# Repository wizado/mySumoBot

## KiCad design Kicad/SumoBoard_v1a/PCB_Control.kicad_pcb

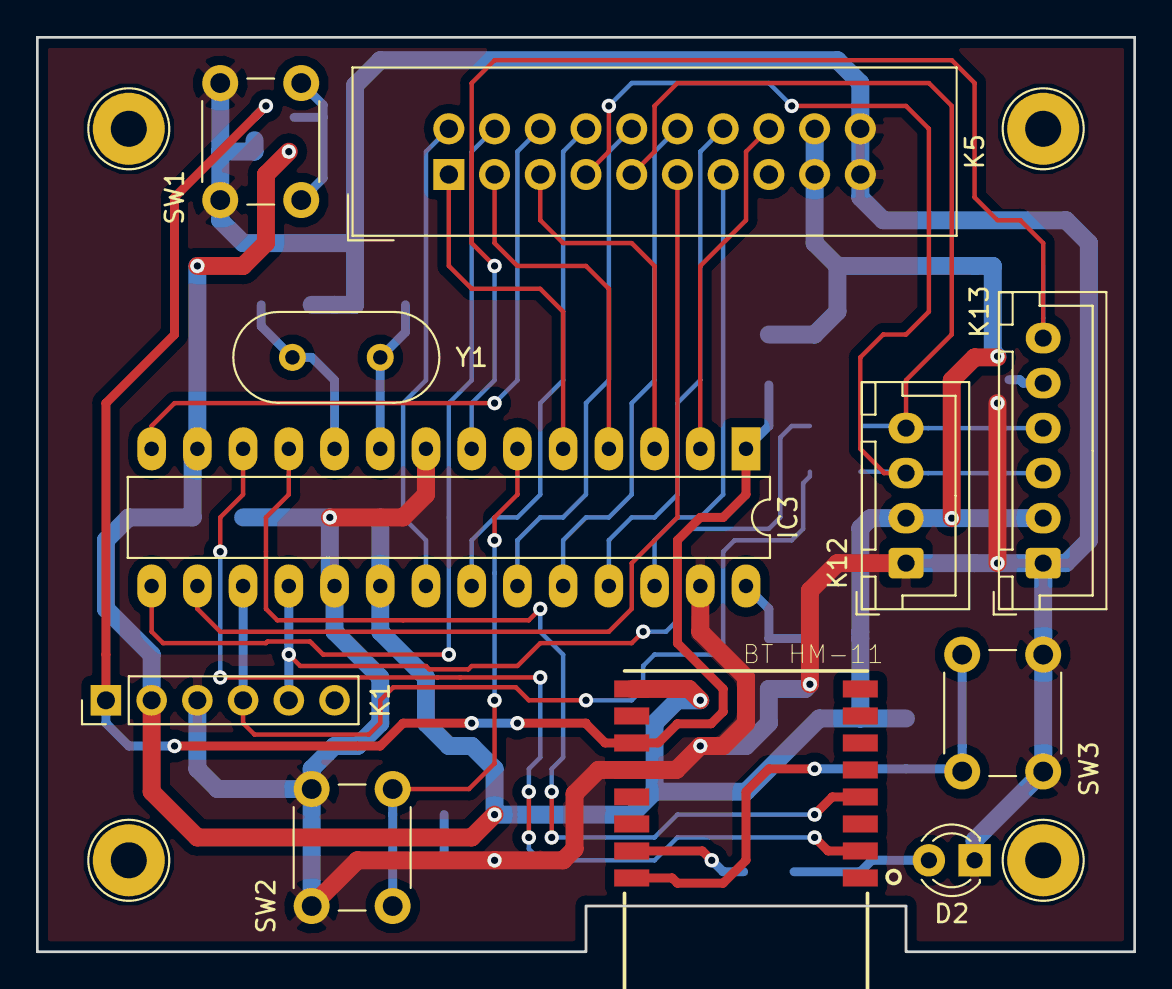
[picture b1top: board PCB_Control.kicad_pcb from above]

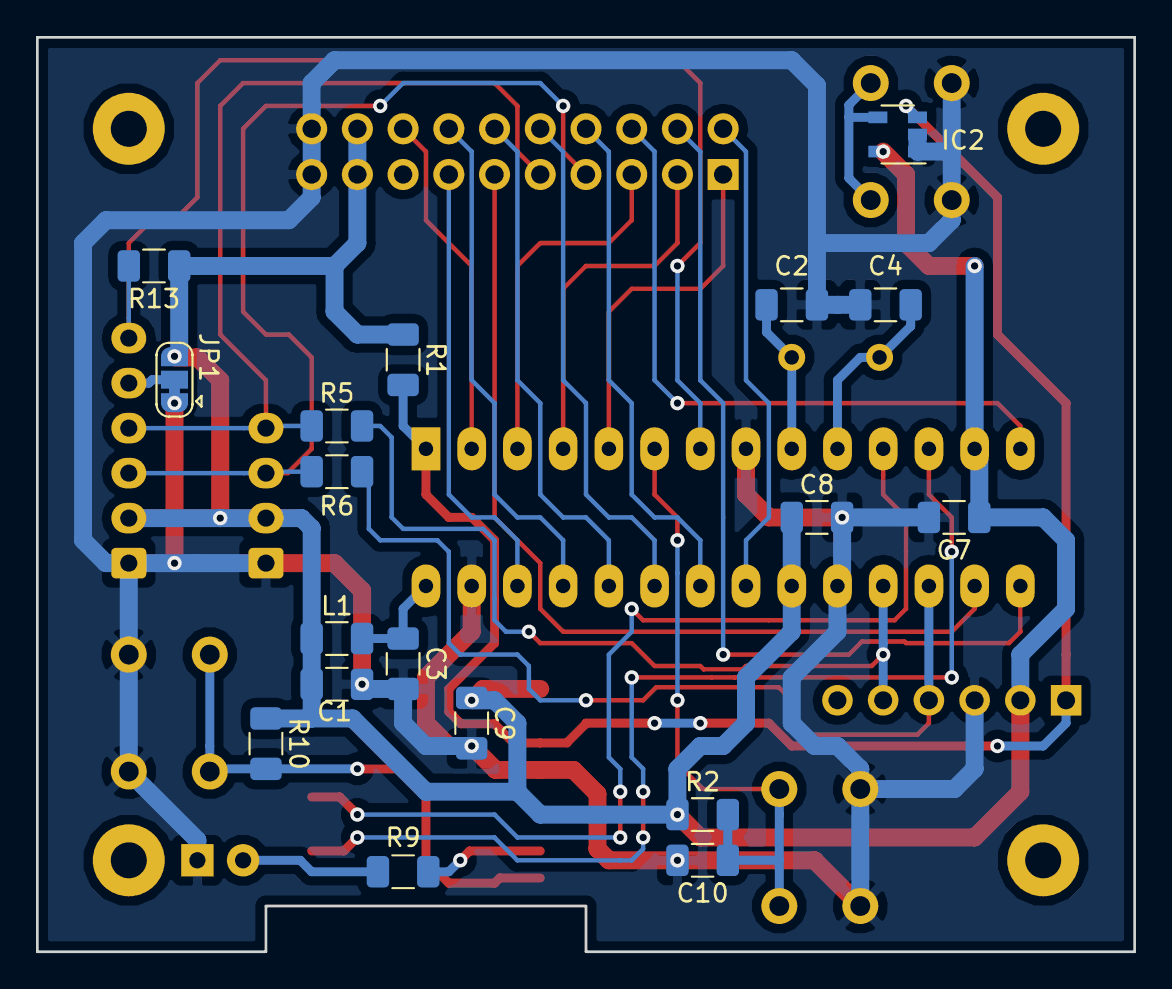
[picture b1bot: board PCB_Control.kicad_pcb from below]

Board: 2 copper layers, 61.0 x 50.8 mm, 29 parts (18 on the bottom side), 32 nets.

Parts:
C1, C3, C7, C8, C9, C10: 100n; C_1206_3216Metric
C2, C4: 22p; C_1206_3216Metric
D2: SYS.; LED_D3.0mm
IC2: LM3724EM5-3.08; SOT-23-5
IC3: DSPIC30F4012; DIP-28_W7.62mm_LongPads
IC4: BT HM-11; XCVR_317030001
JP1: AD0; SolderJumper-3_P1.3mm_Bridged12_RoundedPad1.0x1.5mm
K1: ICSP; PinHeader_1x06_P2.54mm_Vertical
K5: CONTROL; IDC-Header_2x10_P2.54mm_Vertical
K12: AFF OLED; JST_XH_B04B-XH-A_1x04_P2.50mm_Vertical
K13: IMU 6050; JST_XH_B06B-XH-A_1x06_P2.50mm_Vertical
L1: 10u; L_1206_3216Metric
R1, R2, R13: 10k; R_1206_3216Metric
R5, R6: 1.8k; R_1206_3216Metric
R9: 180; R_1206_3216Metric
R10: 1k; R_1206_3216Metric
SW1: RESET; SW_PUSH_6mm
SW2: GAME; SW_PUSH_6mm
SW3: BP SYS.; SW_PUSH_6mm
Y1: 8M; Crystal_HC49-4H_Vertical

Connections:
BPGAME: C10.1, IC3.6, R2.2, SW2.2
CLKO: C4.1, IC3.10, Y1.2
GND: C1.2, C2.2, C3.2, C4.2, C7.2, C8.2, C9.2, C10.2, D2.1, IC2.1, IC2.2, IC3.8, IC3.19, IC3.27, IC4.12, JP1.1, K1.3, K5.19, K5.20, K12.1, K13.1, SW1.1, SW2.1, SW3.2
INT: IC3.7, K13.6, R13.2
MDARC: IC3.5, K5.1
MDAVD: IC3.4, K5.3
MDAVG: IC3.3, K5.5
MDIR1A: IC3.14, K5.6
MDIR1B: IC3.23, K5.10
MDIR2A: IC3.15, K5.4
MDIR2B: IC3.24, K5.12
MPWMA: IC3.21, K5.2
MPWMB: IC3.25, K5.14
MSCL: K5.7, K12.3, K13.3, R6.1
MSDA: K5.9, K12.4, K13.4, R5.1
MSTBY: IC3.22, K5.8
MVBATT: IC3.2, K5.16
MXSHUT1: IC3.16, K5.11
MXSHUT2: IC3.26, K5.13
unnamed: C2.1, IC3.9, Y1.1
unnamed: C3.1, IC3.28, L1.2
unnamed: D2.2, R9.2
unnamed: IC2.4, SW1.2
unnamed: IC4.15, R9.1
unnamed: IC4.16, R10.2, SW3.1
unnamed: JP1.2, K13.5
PGC: IC3.18, K1.5, R5.2
PGD: IC3.17, K1.4, R6.2
U1ARX: IC3.12, IC4.2
U1ATX: IC3.11, IC4.4
VCC: C1.1, C7.1, C8.1, C9.1, IC2.5, IC3.13, IC3.20, IC4.9, JP1.3, K1.2, K5.17, K5.18, K12.2, K13.2, L1.1, R1.1, R2.1, R10.1, R13.1
~MCLR: IC2.3, IC3.1, IC4.11, K1.1, R1.2

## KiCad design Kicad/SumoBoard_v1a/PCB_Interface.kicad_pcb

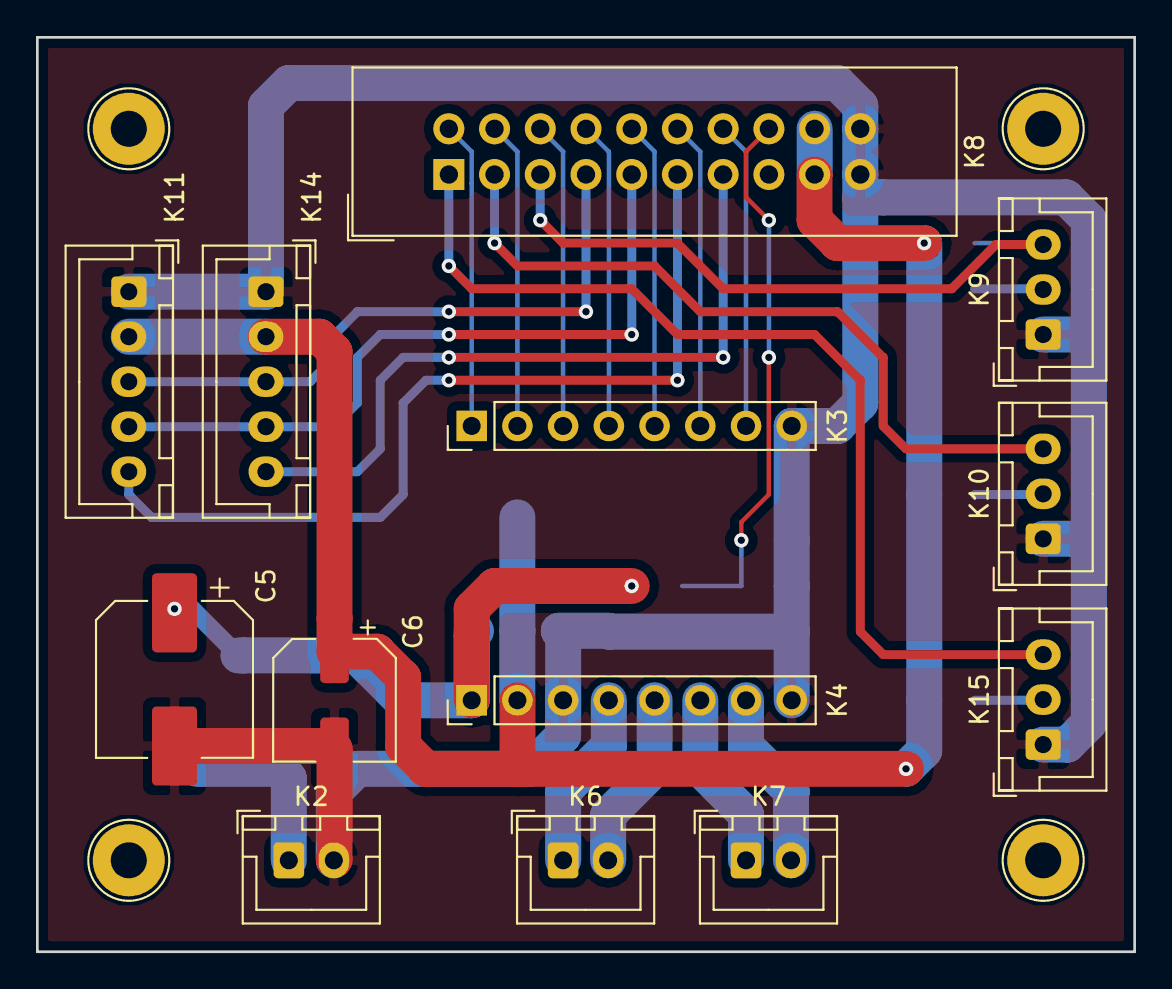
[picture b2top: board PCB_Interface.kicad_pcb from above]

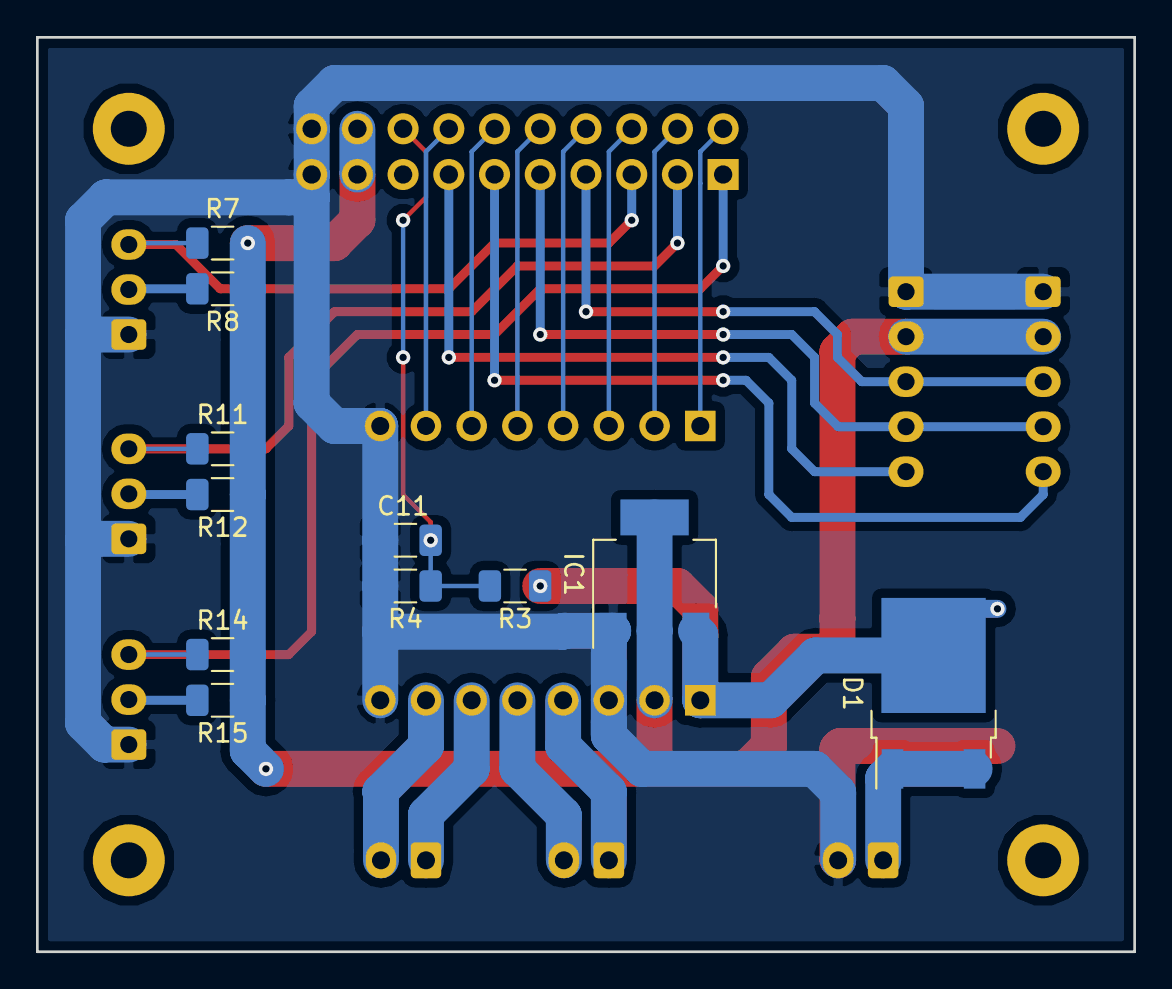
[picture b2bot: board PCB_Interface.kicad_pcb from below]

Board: 2 copper layers, 61.0 x 50.8 mm, 24 parts (11 on the bottom side), 26 nets.

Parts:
C5: 330u; CP_Elec_8x10.5
C6: 100u; CP_Elec_6.3x7.7
C11: 100n; C_1206_3216Metric
D1: MBRD340; TO-252-2
IC1: AP1117-33; SOT-223-3_TabPin2
K2: ALIM; JST_XH_B02B-XH-A_1x02_P2.50mm_Vertical
K3: DRVMA; PinHeader_1x08_P2.54mm_Vertical
K4: DRVMB; PinHeader_1x08_P2.54mm_Vertical
K6: MOT G; JST_XH_B02B-XH-A_1x02_P2.50mm_Vertical
K7: MOT D; JST_XH_B02B-XH-A_1x02_P2.50mm_Vertical
K8: INTERFACE; IDC-Header_2x10_P2.54mm_Vertical
K9: DAVG; JST_XH_B03B-XH-A_1x03_P2.50mm_Vertical
K10: DAVD; JST_XH_B03B-XH-A_1x03_P2.50mm_Vertical
K11: TOF AVANT; JST_XH_B05B-XH-A_1x05_P2.50mm_Vertical
K14: TOF ARRIERE; JST_XH_B05B-XH-A_1x05_P2.50mm_Vertical
K15: DARC; JST_XH_B03B-XH-A_1x03_P2.50mm_Vertical
R3, R4: R; R_1206_3216Metric
R7, R11, R14: 33k; R_1206_3216Metric
R8, R12, R15: 910; R_1206_3216Metric

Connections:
+BATT: C5.1, D1.2, IC1.3, K4.1, R3.1
DARC: K8.1, K15.3, R14.2
DAVD: K8.3, K10.3, R11.2
DAVG: K8.5, K9.3, R7.2
DIR1A: K3.3, K8.6
DIR1B: K3.5, K8.10
DIR2A: K3.2, K8.4
DIR2B: K3.6, K8.12
GND: C5.2, C6.2, C11.2, IC1.1, K2.2, K3.8, K4.3, K4.8, K8.19, K8.20, K9.1, K10.1, K11.1, K14.1, K15.1, R4.2
unnamed: D1.1, D1.3, K2.1
unnamed: K4.4, K6.1
unnamed: K4.5, K6.2
unnamed: K4.6, K7.1
unnamed: K4.7, K7.2
unnamed: K9.2, R8.2
unnamed: K10.2, R12.2
unnamed: K15.2, R15.2
PWMA: K3.1, K8.2
PWMB: K3.7, K8.14
SCL: K8.7, K11.3, K14.3
SDA: K8.9, K11.4, K14.4
STBY: K3.4, K8.8
VBATT: C11.1, K8.16, R3.2, R4.1
VCC: C6.1, IC1.2, K4.2, K8.17, K8.18, K11.2, K14.2, R7.1, R8.1, R11.1, R12.1, R14.1, R15.1
XSHUT1: K8.11, K11.5
XSHUT2: K8.13, K14.5
